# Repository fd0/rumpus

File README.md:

# rumpus

Hard- and Software for the rumpus Atmel AVR development platform.

Helpful links:
 * http://lochraster.org/rumpus
 * http://wiki.lochraster.org/wiki/Rumpus/Aufbauanleitung-v2.html
 * http://wiki.lochraster.org/wiki/Rumpus/Schnellstart.html

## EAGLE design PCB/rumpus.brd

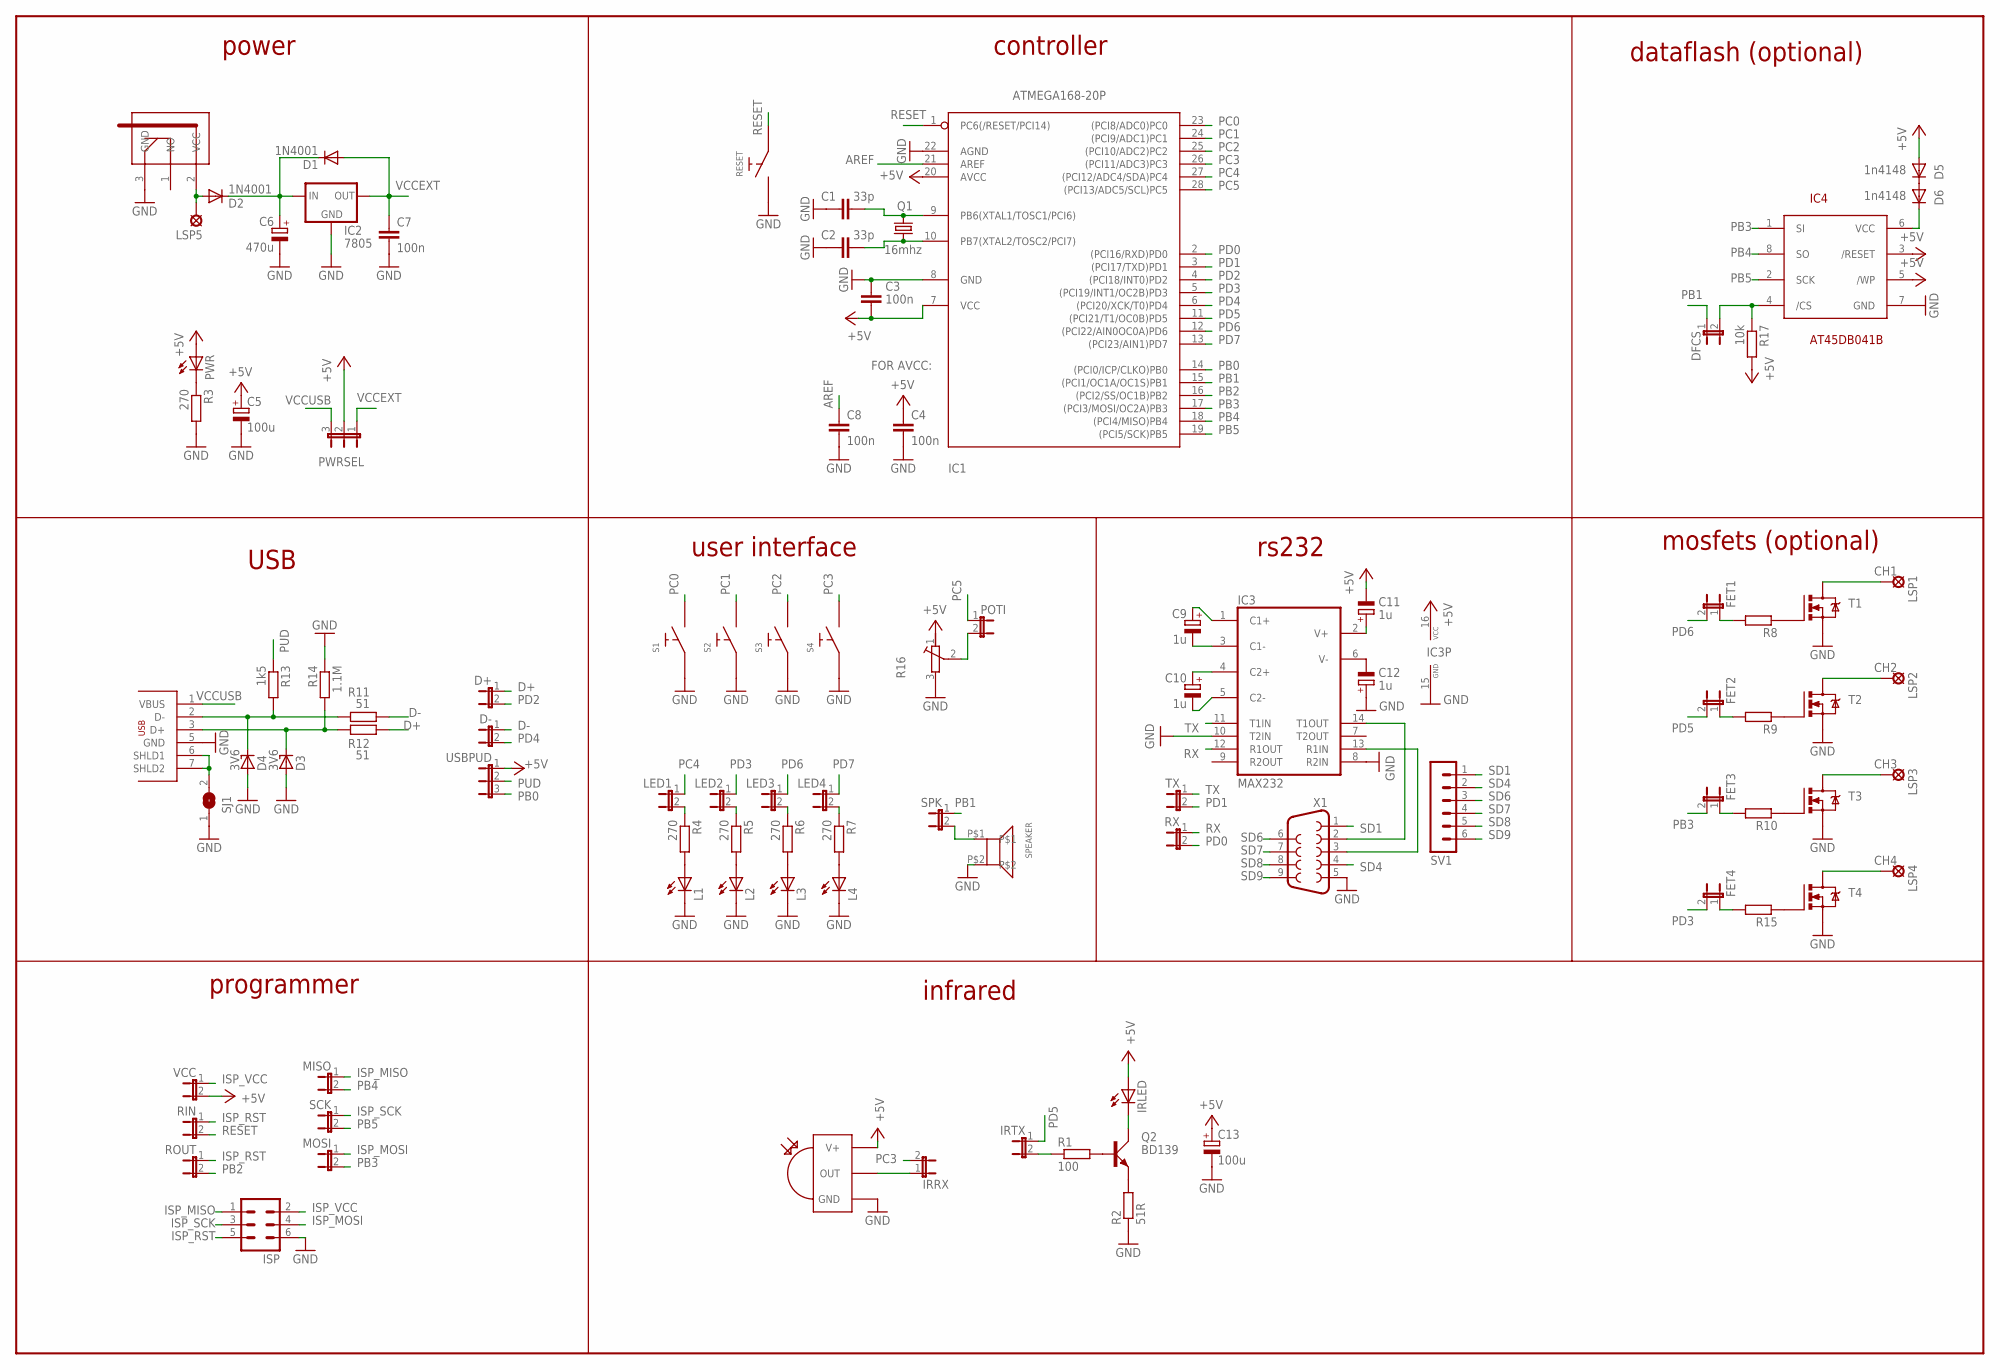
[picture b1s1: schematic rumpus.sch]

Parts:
C1, C2: 33p; C025-024X044
C3, C4, C7, C8: 100n; C025-024X044
C5, C13: 100u; E2,5-6
C6: 470u; E5-10,5
C9, C10, C11, C12: 1u; E2,5-6
D1, D2: 1N4001; DO41-10
D3, D4: 3V6; ZDIO-2.5
D5, D6: 1n4148; D-2.5
D+: JP1E; JP1
D-: JP1E; JP1
DFCS: JP1E; JP1
FET1, FET2, FET3, FET4: JP1E; JP1
IC1: ATMEGA168-20P; DIL28-3
IC2: 7805; 78XXS
IC3: MAX232; DIL16
IC4: AT45DB041B; SOIC8
IRLED: LED5MM
IRRX: JP1E; JP1
IRTX: JP1E; JP1
ISP: MA03-2
L1, L2, L3, L4: LED3MM
LED1, LED2, LED3, LED4: JP1E; JP1
LSP1, LSP2, LSP3, LSP4, LSP5: LSP10
MISO: JP1E; JP1
MOSI: JP1E; JP1
POTI: JP1E; JP1
PWR: LED3MM
PWRSEL: JP2E; JP2
Q1: 16mhz; HC49U-V
Q2: BD139; TO126AV
R1: 100; 0204V
R2: 51R; 0204V
R3: 270; 0204/7
R4, R5, R6, R7: 270; 0204V
R8, R9, R10, R15: R-EU_0204/2V; 0204V
R11, R12: 51; 0204V
R13: 1k5; 0204V
R14: 1.1M; 0204V
R16: R-TRIMMPT6-L; PT6-L
R17: 10k; 0204V
RESET: MIKROTASTER6X6L; TASTER3301
RIN: JP1E; JP1
ROUT: JP1E; JP1
RX: JP1E; JP1
S1, S2, S3, S4: MIKROTASTER6X6L; TASTER3301
SCK: JP1E; JP1
SJ1: SJ
SPEAKER: BUZZER
SPK: JP1E; JP1
SV1: MA06-1
T1, T2, T3, T4: N-CHANNEL-MOSFET; TO220BV
TX: JP1E; JP1
U$2: TSOP1738; TSOP17XX
U$3: HEBW21
USB: USB-SOCKETMINI-B; USB-BWM
USBPUD: JP2E; JP2
VCC: JP1E; JP1
X1: F09HP

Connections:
+5V: C3.2, C4.1, C5.+, C11.-, C13.+, D5.A, IC1.7 (VCC), IC1.20 (AVCC), IC3.16 (VCC), IC4.3 (/RESET), IC4.5 (/WP), IRLED.A, PWR.A, PWRSEL.2, R16.1 (A), R17.2, U$2.V+, USBPUD.1, VCC.2
AREF: C8.1, IC1.21 (AREF)
CH1: LSP1.MP, T1.D
CH2: LSP2.MP, T2.D
CH3: LSP3.MP, T3.D
CH4: LSP4.MP, T4.D
D+: D+.1, R12.2
D-: D-.1, R11.2
GND: C1.2, C2.2, C3.1, C4.2, C5.-, C6.-, C7.2, C8.2, C12.+, C13.-, D3.A, D4.A, IC1.8 (GND), IC1.22 (AGND), IC2.GND, IC3.8 (R2IN), IC3.10 (T2IN), IC3.15 (GND), IC4.7 (GND), ISP.6, L1.K (C), L2.K (C), L3.K (C), L4.K (C), R2.1, R3.2, R14.1, R16.3 (E), RESET.2, S1.1, S2.1, S3.1, S4.1, SJ1.1, SPEAKER.P$2, T1.S, T2.S, T3.S, T4.S, U$2.GND, U$3.3 (GND), USB.5 (GND), X1.5
IR_OUT: IRTX.2, R1.1
ISP_MISO: ISP.1, MISO.1
ISP_MOSI: ISP.4, MOSI.1
ISP_RST: ISP.5, RIN.1, ROUT.1
ISP_SCK: ISP.3, SCK.1
ISP_VCC: ISP.2, VCC.1
unnamed: D2.A, LSP5.MP, U$3.2 (VCC)
unnamed: PWR.K (C), R3.1
unnamed: C1.1, IC1.9 (PB6(XTAL1/TOSC1/PCI6)), Q1.1
unnamed: C6.+, D1.C, D2.C, IC2.IN
unnamed: C2.1, IC1.10 (PB7(XTAL2/TOSC2/PCI7)), Q1.2
unnamed: L1.A, R4.2
unnamed: L2.A, R5.2
unnamed: L3.A, R6.2
unnamed: L4.A, R7.2
unnamed: LED1.2, R4.1
unnamed: LED2.2, R5.1
unnamed: LED3.2, R6.1
unnamed: SJ1.2, USB.6 (SHLD1), USB.7 (SHLD2)
unnamed: D3.C, R12.1, R14.2, USB.3 (D+)
unnamed: D4.C, R11.1, R13.2, USB.2 (D-)
unnamed: LED4.2, R7.1
unnamed: R8.1, T1.G
unnamed: R9.1, T2.G
unnamed: R10.1, T3.G
unnamed: R15.1, T4.G
unnamed: C9.+, IC3.1 (C1+)
unnamed: C9.-, IC3.3 (C1-)
unnamed: C10.+, IC3.4 (C2+)
unnamed: C10.-, IC3.5 (C2-)
unnamed: C11.+, IC3.2 (V+)
unnamed: C12.-, IC3.6 (V-)
unnamed: IC3.13 (R1IN), X1.3
unnamed: IC3.14 (T1OUT), X1.2
unnamed: SPEAKER.P$1, SPK.2
unnamed: IRRX.1, U$2.OUT
unnamed: IRLED.K (C), Q2.C
unnamed: Q2.E, R2.2
unnamed: Q2.B, R1.2
unnamed: FET1.1, R8.2
unnamed: FET2.1, R9.2
unnamed: FET3.1, R10.2
unnamed: FET4.1, R15.2
unnamed: POTI.2, R16.2 (S)
unnamed: D5.C, D6.A
unnamed: D6.C, IC4.6 (VCC)
unnamed: DFCS.2, IC4.4 (/CS), R17.1
PB0: IC1.14 ((PCI0/ICP/CLKO)PB0), USBPUD.3
PB1: DFCS.1, IC1.15 ((PCI1/OC1A/OC1S)PB1), SPK.1
PB2: IC1.16 ((PCI2/SS/OC1B)PB2), ROUT.2
PB3: FET3.2, IC1.17 ((PCI3/MOSI/OC2A)PB3), IC4.1 (SI), MOSI.2
PB4: IC1.18 ((PCI4/MISO)PB4), IC4.8 (SO), MISO.2
PB5: IC1.19 ((PCI5/SCK)PB5), IC4.2 (SCK), SCK.2
PC0: IC1.23 ((PCI8/ADC0)PC0), S1.2
PC1: IC1.24 ((PCI9/ADC1)PC1), S2.2
PC2: IC1.25 ((PCI10/ADC2)PC2), S3.2
PC3: IC1.26 ((PCI11/ADC3)PC3), IRRX.2, S4.2
PC4: IC1.27 ((PCI12/ADC4/SDA)PC4), LED1.1
PC5: IC1.28 ((PCI13/ADC5/SCL)PC5), POTI.1
PD0: IC1.2 ((PCI16/RXD)PD0), RX.2
PD1: IC1.3 ((PCI17/TXD)PD1), TX.2
PD2: D+.2, IC1.4 ((PCI18/INT0)PD2)
PD3: FET4.2, IC1.5 ((PCI19/INT1/OC2B)PD3), LED2.1
PD4: D-.2, IC1.6 ((PCI20/XCK/T0)PD4)
PD5: FET2.2, IC1.11 ((PCI21/T1/OC0B)PD5), IRTX.1
PD6: FET1.2, IC1.12 ((PCI22/AIN0OC0A)PD6), LED3.1
PD7: IC1.13 ((PCI23/AIN1)PD7), LED4.1
PUD: R13.1, USBPUD.2
RESET: IC1.1 (PC6(/RESET/PCI14)), RESET.1, RIN.2
RX: IC3.12 (R1OUT), RX.1
SD1: SV1.1, X1.1
SD4: SV1.2, X1.4
SD6: SV1.3, X1.6
SD7: SV1.4, X1.7
SD8: SV1.5, X1.8
SD9: SV1.6, X1.9
TX: IC3.11 (T1IN), TX.1
VCCEXT: C7.1, D1.A, IC2.OUT, PWRSEL.1
VCCUSB: PWRSEL.3, USB.1 (VBUS)

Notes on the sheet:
FOR AVCC:
power
controller
dataflash (optional)
mosfets (optional)
USB
user interface
rs232
infrared
programmer

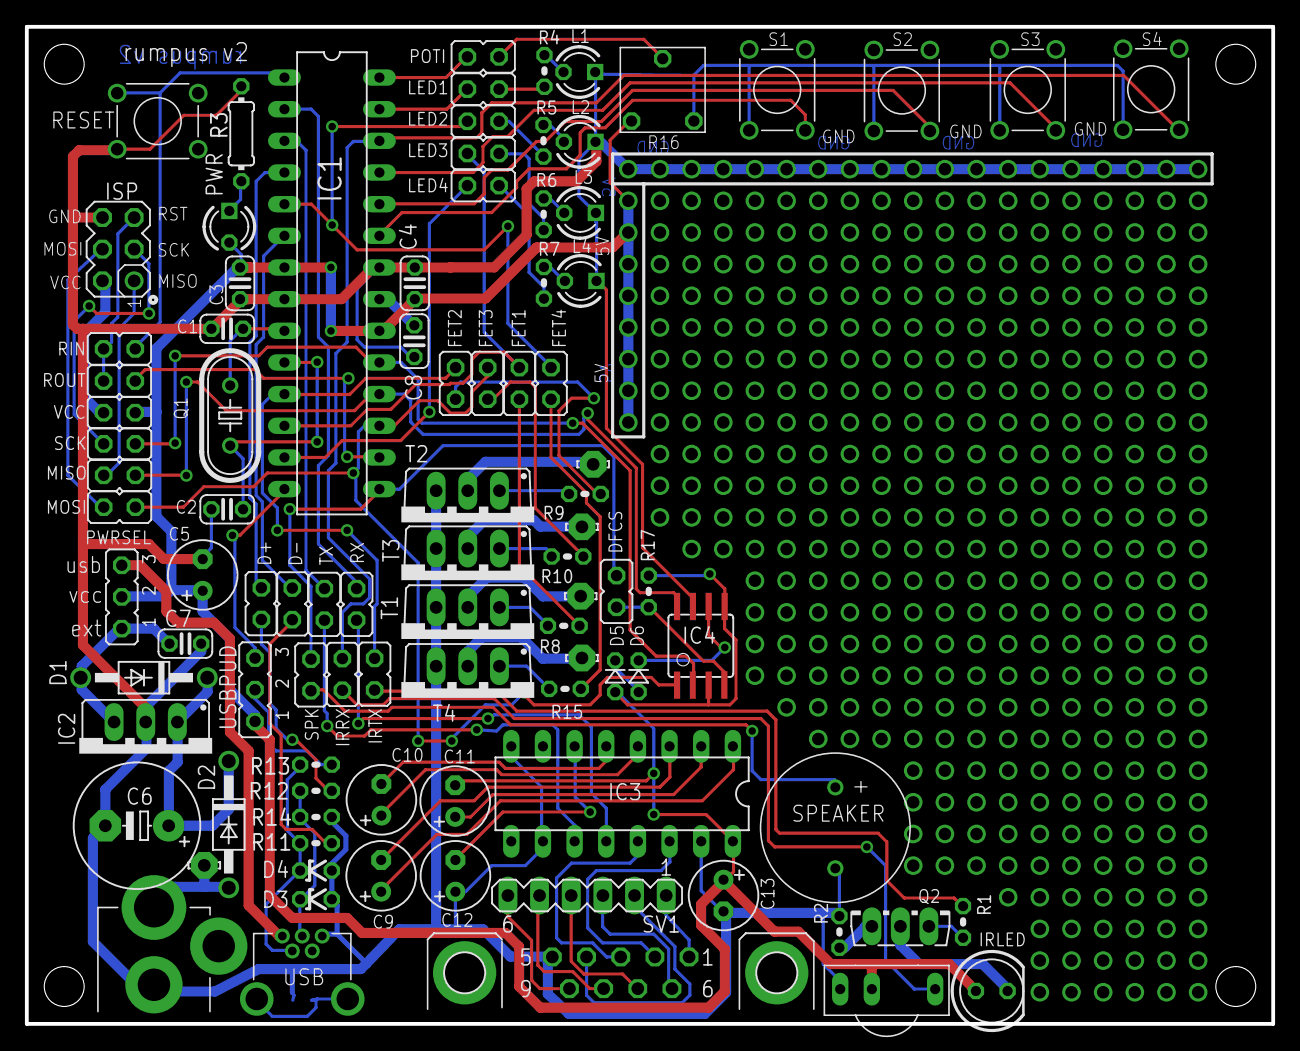
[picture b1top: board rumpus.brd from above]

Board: 2 copper layers, 100.0 x 80.0 mm, 95 parts (1 on the bottom side), 88 nets.

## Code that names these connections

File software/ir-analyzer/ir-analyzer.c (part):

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    VIEW_DECODED = 3,
} view = VIEW_VALUE_AND_TIME;

/* call every 10 ms, for buttons at pins PC0-PC3 */
static uint8_t button_sample(void)
{
    /* initialize state, buttons are active low! */
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    }

    /* toggle second led */
    PORTD ^= _BV(PD3);

    /* toggle state */
    state = !state;
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        done = 1;

        /* turn on third led */
        PORTD |= _BV(PD6);
    }
}

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    uart_printf("rumpus ir analyzer\n");

    /* configure led pins as outputs and turn leds off */
    DDRC |= _BV(PC4);
    DDRD |= _BV(PD3) | _BV(PD6) | _BV(PD7);
    PORTC &= ~_BV(PC4);
    PORTD &= ~(_BV(PD3) | _BV(PD6) | _BV(PD7));

    /* configure ir input pin, with pullup */
    DDRC &= ~_BV(PC3);
    PORTC |= _BV(PC3);

    /* configure button input pins, with pullup */
    DDRC &= ~(_BV(PC0) | _BV(PC1) | _BV(PC2) | _BV(PC3));
    PORTC |= _BV(PC0) | _BV(PC1) | _BV(PC2) | _BV(PC3);

    /* wait until pin is high (no ir carrier is detected) */
    while(!(PINC & _BV(PC3)));

    /* enable pin change interrupt 1 for ir input pin (PC3/PCINT11) */
    PCMSK1 |= _BV(PCINT11);
    PCICR |= _BV(PCIE1);

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    TIMSK2 = _BV(OCIE2A);

    /* signal user availability by turning on led 1 */
    PORTC |= _BV(PC4);

    /* enable interrupts */
    sei();

    /* signal the user that the analyzer part has started by turning led 1 on */
    PORTC |= _BV(PC3);

    while(1) {
        /* if a code has been received */
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            }

            /* turn off second and third led */
            PORTD &= ~(_BV(PD3) | _BV(PD6));

            /* wait until pin is high (no ir carrier is detected) */
            while(!(PINC & _BV(PC3)));

            /* reset all global variables */
            pos = 0;
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                    PCMSK1 &= ~_BV(PCINT11);

                    /* turn off led1 */
                    PORTC &= ~_BV(PC4);

                } else if (mode == MODE_DISPLAY) {
                    uart_printf("scan and display codes\n");
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                    PCMSK1 |= _BV(PCINT11);

                    /* turn on led1 */
                    PORTC |= _BV(PC4);
                }
            }

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
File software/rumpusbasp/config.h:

/* configuration file for rumpusbasp */

#include "macros.h"

/* uncomment this if you want a usb echo function (for communication testing) */
//#define ENABLE_ECHO_FUNC

/* uncomment this for debug information via uart */
//#define DEBUG_UART

/* isp pins */
#define SPI_PORTNAME    B
#define SPI_SS      PB2
#define SPI_MOSI    PB3
#define SPI_MISO    PB4
#define SPI_SCK     PB5

/* led pins */
#define LED1_PORTNAME   C
#define LED1_PIN        PC4
#if HARDWARE == 1
    #define LED2_PORTNAME   C
    #define LED2_PIN        PC5
#else
    #define LED2_PORTNAME   D
    #define LED2_PIN        PD3
#endif

/* try to connect to device at lowest spi data rate */
#define SPI_MAX_TRIES   32

/* maximum eeprom and flash write timeouts (for _delay_loop_2) */
#define EEPROM_TIMEOUT  (F_CPU/100/4)       /* 10ms */
#define EEPROM_POLL_TIMEOUT (F_CPU/10000/4) /* 100uS */
#define EEPROM_POLL_TRIES   100             /* 100 times */
#define FLASH_TIMEOUT   (F_CPU/200/4)       /* 5ms */
#define FLASH_POLL_TIMEOUT  (F_CPU/10000/4) /* 100uS */
#define FLASH_POLL_TRIES    50              /* 50 times */
#define FLASH_PAGE_TIMEOUT   (F_CPU/100/4)       /* 10ms */
#define FLASH_PAGE_POLL_TIMEOUT  (F_CPU/10000/4) /* 100uS */
#define FLASH_PAGE_POLL_TRIES    100             /* 100 times */

/* more macros */
#define SPI_PORT    _OUTPORT(SPI_PORTNAME)
#define SPI_DDR     _DDRPORT(SPI_PORTNAME)

#define LED1_DDR    _DDRPORT(LED1_PORTNAME)
#define LED1_PORT   _OUTPORT(LED1_PORTNAME)
#define LED2_DDR    _DDRPORT(LED2_PORTNAME)
#define LED2_PORT   _OUTPORT(LED2_PORTNAME)

#define LED1_ON()   LED1_PORT |= _BV(LED1_PIN)
#define LED1_OFF()  LED1_PORT &= ~_BV(LED1_PIN)
#define LED1_TOGGLE()   LED1_PORT ^= _BV(LED1_PIN)
#define LED2_ON()   LED2_PORT |= _BV(LED2_PIN)
#define LED2_OFF()  LED2_PORT &= ~_BV(LED2_PIN)
#define LED2_TOGGLE()   LED2_PORT ^= _BV(LED2_PIN)

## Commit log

2016-03-28 Initial import
2016-03-28 Add docs
2016-06-07 Fix typos
